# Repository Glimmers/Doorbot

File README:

Doorbot -- Internet enabled doorbell discord bot
================================================

This project contains the files and schematics needed to build a raspberry-pi compatible doorbell
which will send a message to a Discord channel.

Dependencies
------------

*    A Raspberry Pi running Raspbian
*    The following packages
        python3
        python3-rpi.gpio
        python3-requests
*    A Discord account
*    A webhook set up for the discord channel you want your messages to go to. For instructions on
      setting up a webhook, visit
      https://support.discordapp.com/hc/en-us/articles/228383668-Intro-to-Webhooks

Software Installation instructions
----------------------------------

1. Download the package to your pi.

    *   Via git: git clone https://github.com/Glimmers/Doorbot.git doorbot

    *   Via wget: wget https://github.com/Glimmers/Doorbot/archive/master.zip

2. Run the included install.sh shell script to add the requisite service user, install dependencies,
copy the files into the service user's directory, and install the systemd service.

3. Copy the example discord.ini file to the actual ini file, and fill out the fields inside. At a
minimum, you will need to replace all the values in the [Doorbot] section.

    a) If you're not using a camera, set UseCamera = no .

    b) If you are using a Camera, fill out the [Camera] section with the access type, hostname,
    username and password if needed, and path to get an image. For example, if the URL to get an image
    from the camera is: http://hostname/path/to/image.cgi , you'll want to set the config values as:

        [Camera]
        Protocol = http
        Host = hostname
        Path = /path/to/image.cgi

4. Enable the doorbot service
    
        sudo systemctl enable doorbot.service

5. Start the doorbot service

        sudo systemctl start doorbot.service

Hardware Installation Instructions
----------------------------------

In the Eagle Schematics directory, there are schematics in Eagle 7.x format for two variants of sense
boards. The first -- Doorbell.sch -- is a basic 1-transistor schematic. The second --
DoorbellBothRelayBJT.sch -- is the 3-transistor schematic which has better noise tolerance. For both of
these circuits, hooking up to the Pi side of the board is the same. Pin 1 goes to the +3.3 volt supply
pin of the Pi (pin 1 or pin 17). Pin 2 goes to one of the GPIO pins, typically pin 37. Pin 3 goes to
Ground (any one of pin 6, 9, 14, 20, 25, 30, 34, or 39).

*     For the 1 transistor schematic, pin 1 of the relay side goes to the Normally Open pin of the
      relay. Pin 3 of the relay goes to the common side. Pin 2 is for testing, and not used for normal
      operation.

*     For the 3-transistor schematic, pin one of the relay side goes to the Normally Open pin of the
      relay. Pin 2 goes to the Common pin of the relay. Pin 3 goes to the Normally Closed pin.

For hooking the relay up to the chime, typically you'll hook the coil leads so one is going to the
terminal labelled "Trans" and the other to the terminal labelled "Front". While hooking it up, you'll
want to either disconnect the doorbell transformer, or have someone watching the door to
avoid the risk of getting shocked while hooking it up.

For Testing/Development
-----------------------

The one-transistor board has a provision for testing, which is useful in developing the software for
the board. In testing, remove the board from the relay, and hook a 2N2222 or 2N3904 transistor to the
relay header, with pin 1 of the transistor corresponding to pin 1 of the socket, pin 2 of the
transistor going to pin 2 of the socket, and pin 3 going to pin 3. The test pin should go to one of the
GPIO leads of the PI, typically pin 35.

License
-------

This project is available under the 2-clause BSD license. For details of the license, see the LICENSE file.

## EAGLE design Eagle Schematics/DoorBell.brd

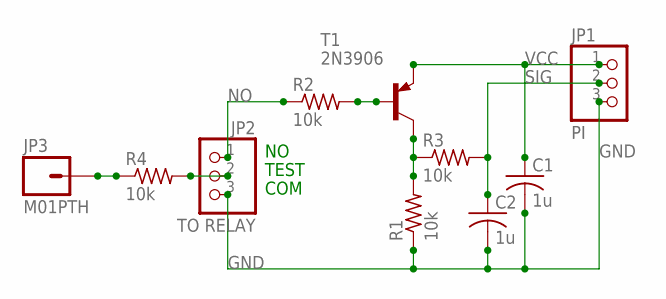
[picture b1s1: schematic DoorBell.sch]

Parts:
C1, C2: 1u; C025-025X050
JP1: PI; 1X03
JP2: TO RELAY; 1X03
JP3: M01PTH; 1X01
R1, R2, R3, R4: 10k; 0204/5
T1: 2N3906; TO92-EBC

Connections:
GND: C1.2, C2.2, JP1.3, JP2.3, R1.1
unnamed: R1.2, R3.1, T1.C
unnamed: R2.2, T1.B
unnamed: JP2.2, R4.2
unnamed: JP3.1, R4.1
NO: JP2.1, R2.1
SIG: C2.1, JP1.2, R3.2
VCC: C1.1, JP1.1, T1.E

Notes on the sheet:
TEST
COM

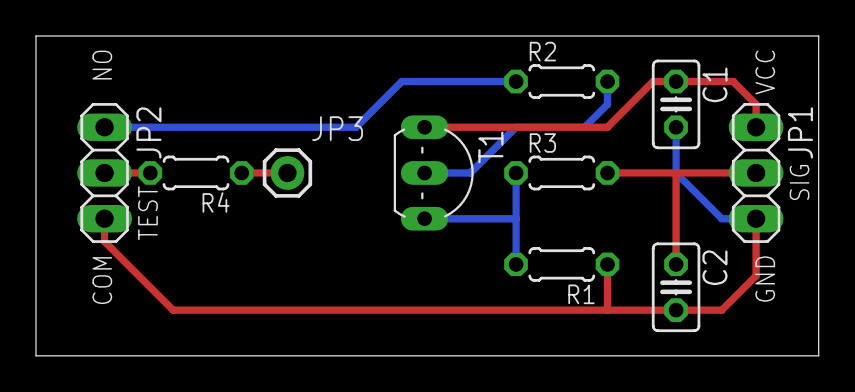
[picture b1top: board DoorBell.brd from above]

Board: 2 copper layers, 43.5 x 17.8 mm, 10 parts (0 on the bottom side), 8 nets.

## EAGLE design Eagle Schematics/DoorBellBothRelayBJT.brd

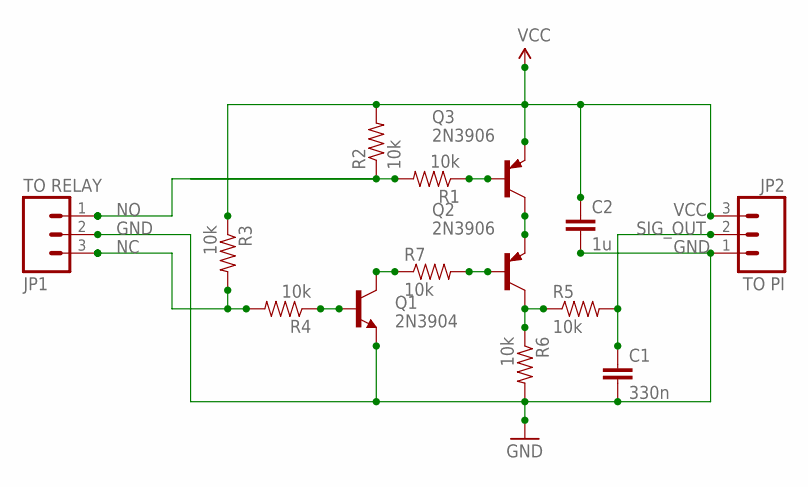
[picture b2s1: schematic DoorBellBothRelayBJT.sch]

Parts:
C1: 330n; CAP-PTH-SMALL-KIT
C2: 1u; CAP-PTH-SMALL-KIT
JP1: TO RELAY; 1X03_NO_SILK
JP2: TO PI; 1X03_NO_SILK
Q1: 2N3904; TO-92
Q2, Q3: 2N3906; TO92
R1, R2, R3, R4, R5, R6, R7: 10k; AXIAL-0.3EZ

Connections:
GND: C1.2, C2.2, JP1.2, JP2.1, Q1.1 (E), R6.P$2 (2)
unnamed: Q1.3 (C), R7.P$1 (1)
unnamed: Q2.2 (B), R7.P$2 (2)
unnamed: Q1.2 (B), R4.P$1 (1)
unnamed: Q3.2 (B), R1.P$1 (1)
unnamed: Q2.3 (E), Q3.1 (C)
unnamed: Q2.1 (C), R5.P$1 (1), R6.P$1 (1)
NC: JP1.3, R3.P$2 (2), R4.P$2 (2)
NO: JP1.1, R1.P$2 (2), R2.P$1 (1)
SIG_OUT: C1.1, JP2.2, R5.P$2 (2)
VCC: C2.1, JP2.3, Q3.3 (E), R2.P$2 (2), R3.P$1 (1)

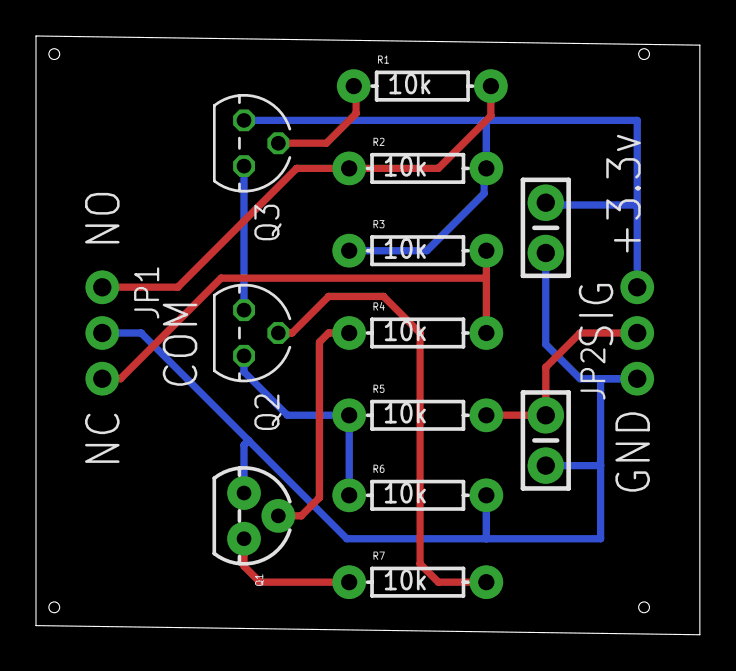
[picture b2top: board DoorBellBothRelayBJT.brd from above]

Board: 2 copper layers, 36.9 x 33.3 mm, 14 parts (0 on the bottom side), 11 nets.

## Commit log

2019-01-08 Initial recommit. Previous history wiped to clear live settings.
2019-01-08 Replaced hardcoded value for active pin with the variable it refers to
2019-01-08 Minor cleanup, changed wording on some comments/error messages
2019-01-08 Changed permissions
2019-01-14 Cleared out PID file to prevent potential issues when running
2019-01-14 Updated install.sh to install requisite python libraries
2019-01-14 Fix code so it pulls the sensor_pin value from the config so the code starts, fix unit file so it sets the working directory properly
2019-01-14 Added schematics and board layout
2019-01-14 Added basic doorbell schematic
2019-01-14 Improved Board Labels
2019-01-14 Added license text. Added README
2019-01-14 Formatting README
2019-01-14 Rename README to README.md
2019-01-14 More formatting
2019-01-14 Formatting
2019-01-14 Last bit of formatting

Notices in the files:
parts and their libraries:
SparkFun-Connectors: Licensing: Creative Commons ShareAlike 4.0 International - https://creativecommons.org/licenses/by-sa/4.0
